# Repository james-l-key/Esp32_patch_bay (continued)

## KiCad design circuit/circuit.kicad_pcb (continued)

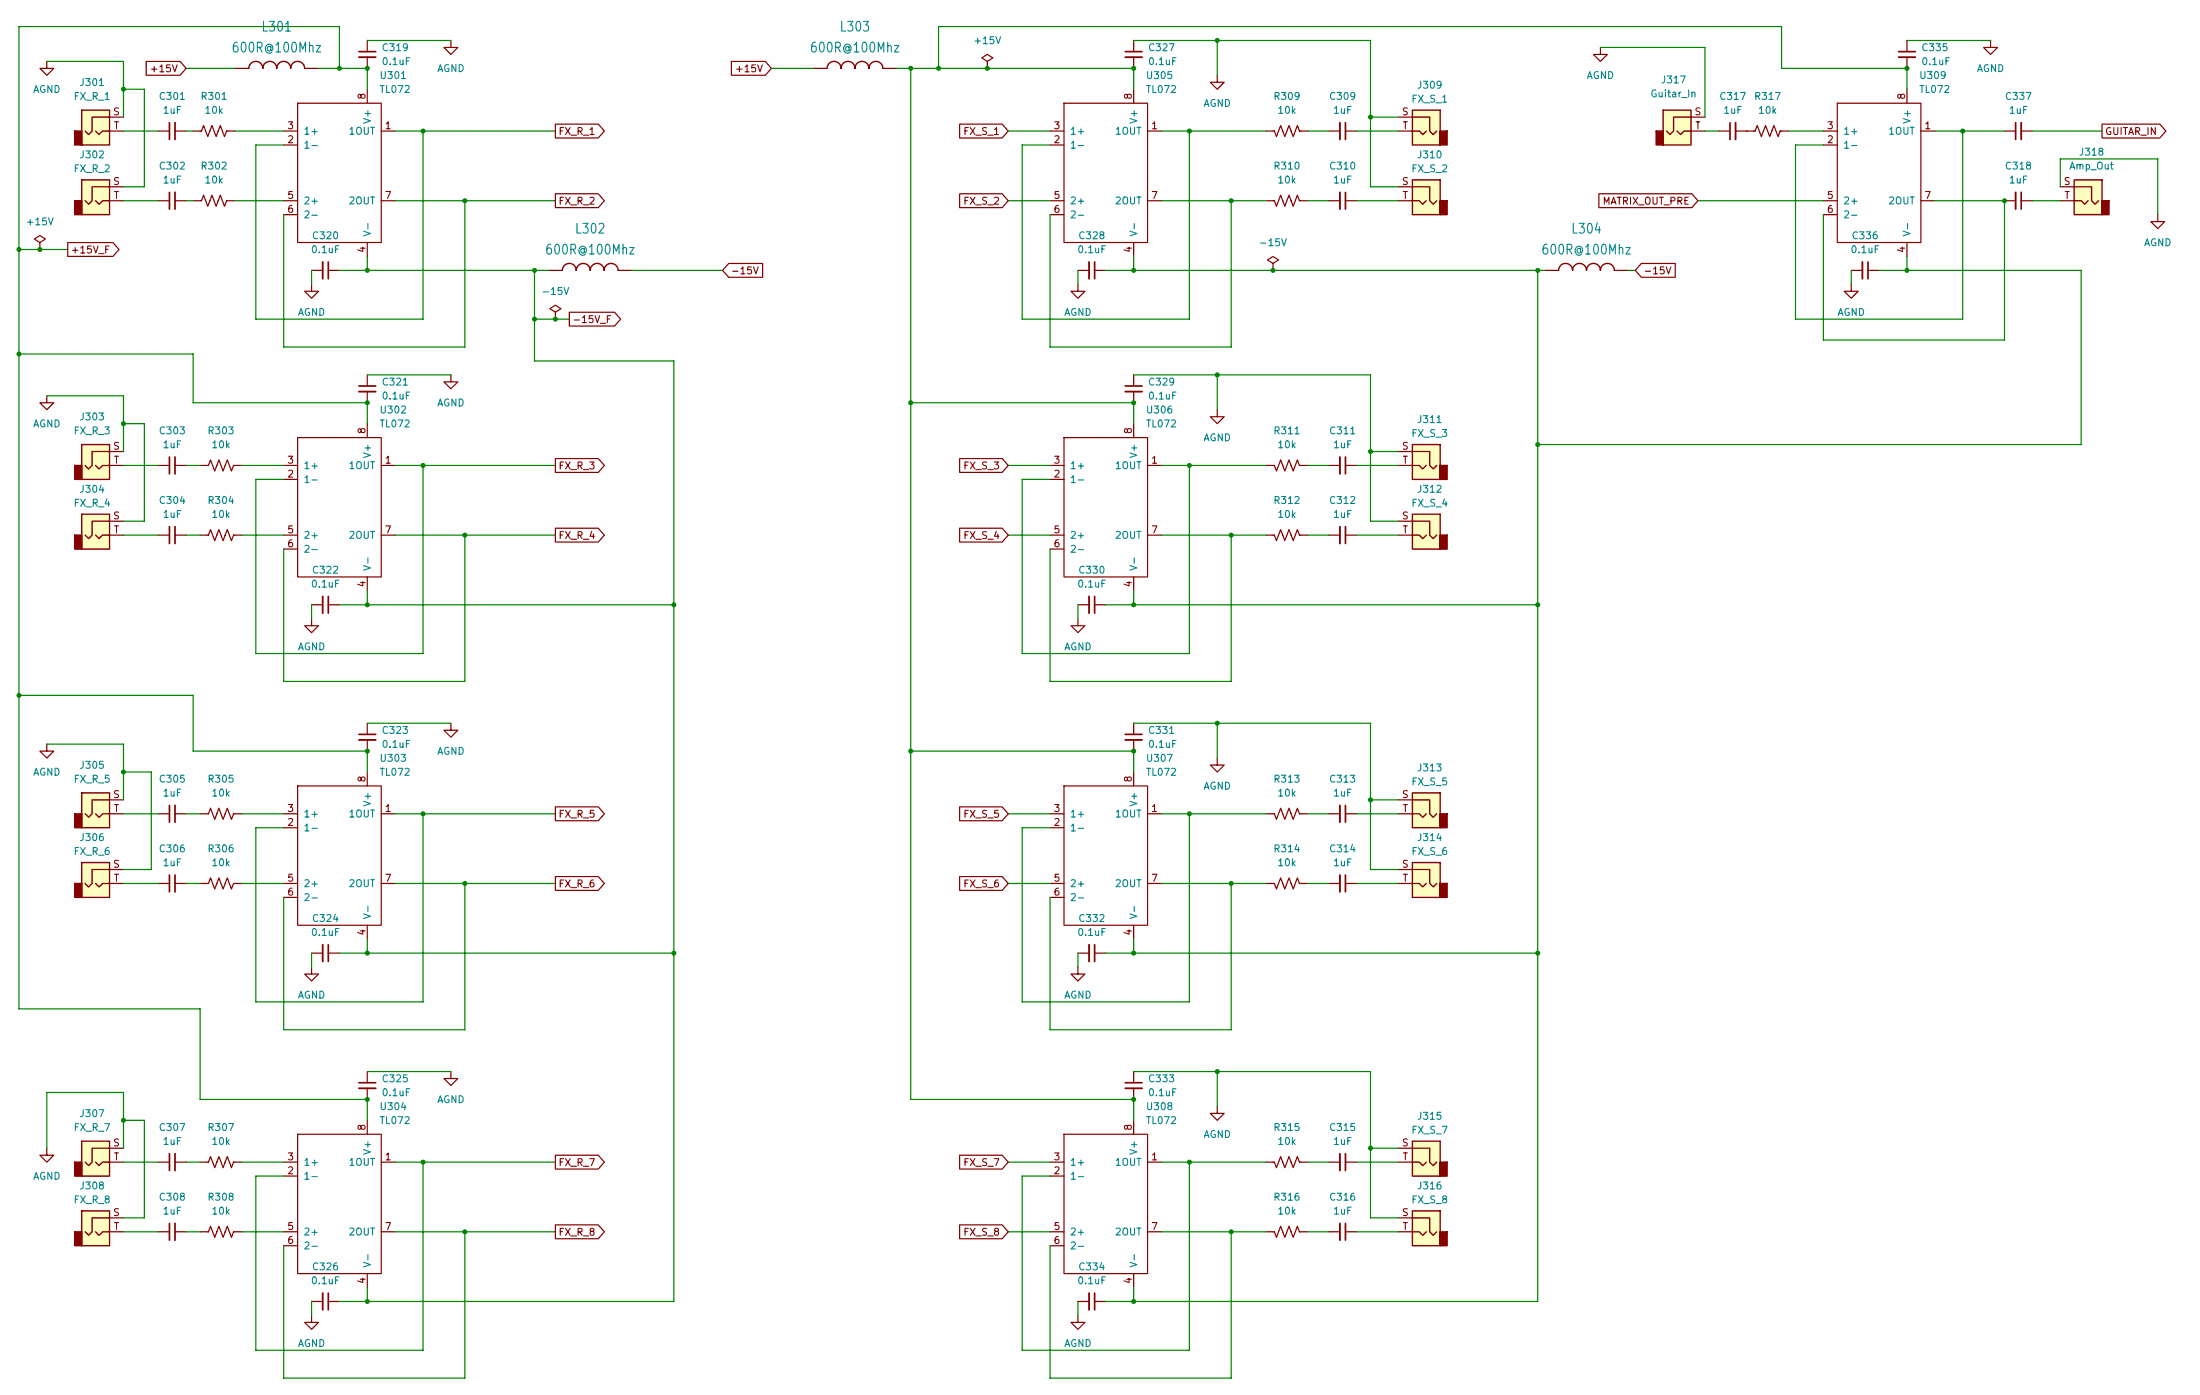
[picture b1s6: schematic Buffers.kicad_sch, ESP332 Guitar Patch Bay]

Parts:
C301, C302, C303, C304, C305, C306, C307, C308, C309, C310, C311, C312, C313, C314, C315, C316, C317, C318, C337: 1uF; C_Disc_D5.0mm_W2.5mm_P2.50mm
C319, C320, C321, C322, C323, C324, C325, C326, C327, C328, C329, C330, C331, C332, C333, C334, C335, C336: 0.1uF; C_Disc_D5.0mm_W2.5mm_P2.50mm
J301: FX_R_1; Jack
J302: FX_R_2; Jack
J303: FX_R_3; Jack
J304: FX_R_4; Jack
J305: FX_R_5; Jack
J306: FX_R_6; Jack
J307: FX_R_7; Jack
J308: FX_R_8; Jack
J309: FX_S_1; Jack
J310: FX_S_2; Jack
J311: FX_S_3; Jack
J312: FX_S_4; Jack
J313: FX_S_5; Jack
J314: FX_S_6; Jack
J315: FX_S_7; Jack
J316: FX_S_8; Jack
J317: Guitar_In; Jack
J318: Amp_Out; Jack
L301, L302, L303, L304: 600R@100Mhz; WE-UKW_74275010
R301, R302, R303, R304, R305, R306, R307, R308, R309, R310, R311, R312, R313, R314, R315, R316, R317: 10k; R_Axial_DIN0207_L6.3mm_D2.5mm_P7.62mm_Horizontal
U301, U302, U303, U304, U305, U306, U307, U308, U309: TL072; DIP-8_W7.62mm

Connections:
+15V: L301.2, L303.1; also elsewhere on the board
+15V_F: C319.2, C321.2, C323.2, C325.2, L301.1, U301.8 (V+), U302.8 (V+), U303.8 (V+), U304.8 (V+); also elsewhere on the board
-15V: L302.1, L304.2; also elsewhere on the board
-15V_F: C320.1, C322.1, C324.1, C326.1, L302.2, U301.4 (V-), U302.4 (V-), U303.4 (V-), U304.4 (V-); also elsewhere on the board
AGND: C319.1, C320.2, C321.1, C322.2, C323.1, C324.2, C325.1, C326.2, C327.1, C328.2, C329.1, C330.2, C331.1, C332.2, C333.1, C334.2, C335.1, C336.2, J301.S, J302.S, J303.S, J304.S, J305.S, J306.S, J307.S, J308.S, J309.S, J310.S, J311.S, J312.S, J313.S, J314.S, J315.S, J316.S, J317.S, J318.S; also elsewhere on the board
FX_R_1: U301.1 (1OUT), U301.2 (1-); also elsewhere on the board
FX_R_2: U301.6 (2-), U301.7 (2OUT); also elsewhere on the board
FX_R_3: U302.1 (1OUT), U302.2 (1-); also elsewhere on the board
FX_R_4: U302.6 (2-), U302.7 (2OUT); also elsewhere on the board
FX_R_5: U303.1 (1OUT), U303.2 (1-); also elsewhere on the board
FX_R_6: U303.6 (2-), U303.7 (2OUT); also elsewhere on the board
FX_R_7: U304.1 (1OUT), U304.2 (1-); also elsewhere on the board
FX_R_8: U304.6 (2-), U304.7 (2OUT); also elsewhere on the board
FX_S_1: U305.3 (1+); also elsewhere on the board
FX_S_2: U305.5 (2+); also elsewhere on the board
FX_S_3: U306.3 (1+); also elsewhere on the board
FX_S_4: U306.5 (2+); also elsewhere on the board
FX_S_5: U307.3 (1+); also elsewhere on the board
FX_S_6: U307.5 (2+); also elsewhere on the board
FX_S_7: U308.3 (1+); also elsewhere on the board
FX_S_8: U308.5 (2+); also elsewhere on the board
GUITAR_IN: C337.2; also elsewhere on the board
MATRIX_OUT_PRE: U309.5 (2+); also elsewhere on the board
unnamed: C301.1, J301.T
unnamed: C301.2, R301.2
unnamed: C302.1, J302.T
unnamed: C302.2, R302.2
unnamed: C303.1, J303.T
unnamed: C303.2, R303.2
unnamed: C304.1, J304.T
unnamed: C304.2, R304.2
unnamed: C305.1, J305.T
unnamed: C305.2, R305.2
unnamed: C306.1, J306.T
unnamed: C306.2, R306.2
unnamed: C307.1, J307.T
unnamed: C307.2, R307.2
unnamed: C308.1, J308.T
unnamed: C308.2, R308.2
unnamed: C309.1, J309.T
unnamed: C309.2, R309.2
unnamed: C310.1, J310.T
unnamed: C310.2, R310.2
unnamed: C311.1, J311.T
unnamed: C311.2, R311.2
unnamed: C312.1, J312.T
unnamed: C312.2, R312.2
unnamed: C313.1, J313.T
unnamed: C313.2, R313.2
unnamed: C314.1, J314.T
unnamed: C314.2, R314.2
unnamed: C315.1, J315.T
unnamed: C315.2, R315.2
unnamed: C316.1, J316.T
unnamed: C316.2, R316.2
unnamed: C317.1, J317.T
unnamed: C317.2, R317.2
unnamed: C318.1, J318.T
unnamed: R301.1, U301.3 (1+)
unnamed: R302.1, U301.5 (2+)
unnamed: R303.1, U302.3 (1+)
unnamed: R304.1, U302.5 (2+)
unnamed: R305.1, U303.3 (1+)
unnamed: R306.1, U303.5 (2+)
unnamed: R307.1, U304.3 (1+)
unnamed: R308.1, U304.5 (2+)
unnamed: R309.1, U305.1 (1OUT), U305.2 (1-)
unnamed: R310.1, U305.6 (2-), U305.7 (2OUT)
unnamed: C327.2, C329.2, C331.2, C333.2, C335.2, L303.2, U305.8 (V+), U306.8 (V+), U307.8 (V+), U308.8 (V+), U309.8 (V+)
unnamed: C328.1, C330.1, C332.1, C334.1, C336.1, L304.1, U305.4 (V-), U306.4 (V-), U307.4 (V-), U308.4 (V-), U309.4 (V-)
unnamed: R311.1, U306.1 (1OUT), U306.2 (1-)
unnamed: R312.1, U306.6 (2-), U306.7 (2OUT)
unnamed: R313.1, U307.1 (1OUT), U307.2 (1-)
unnamed: R314.1, U307.6 (2-), U307.7 (2OUT)
unnamed: R315.1, U308.1 (1OUT), U308.2 (1-)
unnamed: R316.1, U308.6 (2-), U308.7 (2OUT)
unnamed: R317.1, U309.3 (1+)
unnamed: C337.1, U309.1 (1OUT), U309.2 (1-)
unnamed: C318.2, U309.6 (2-), U309.7 (2OUT)

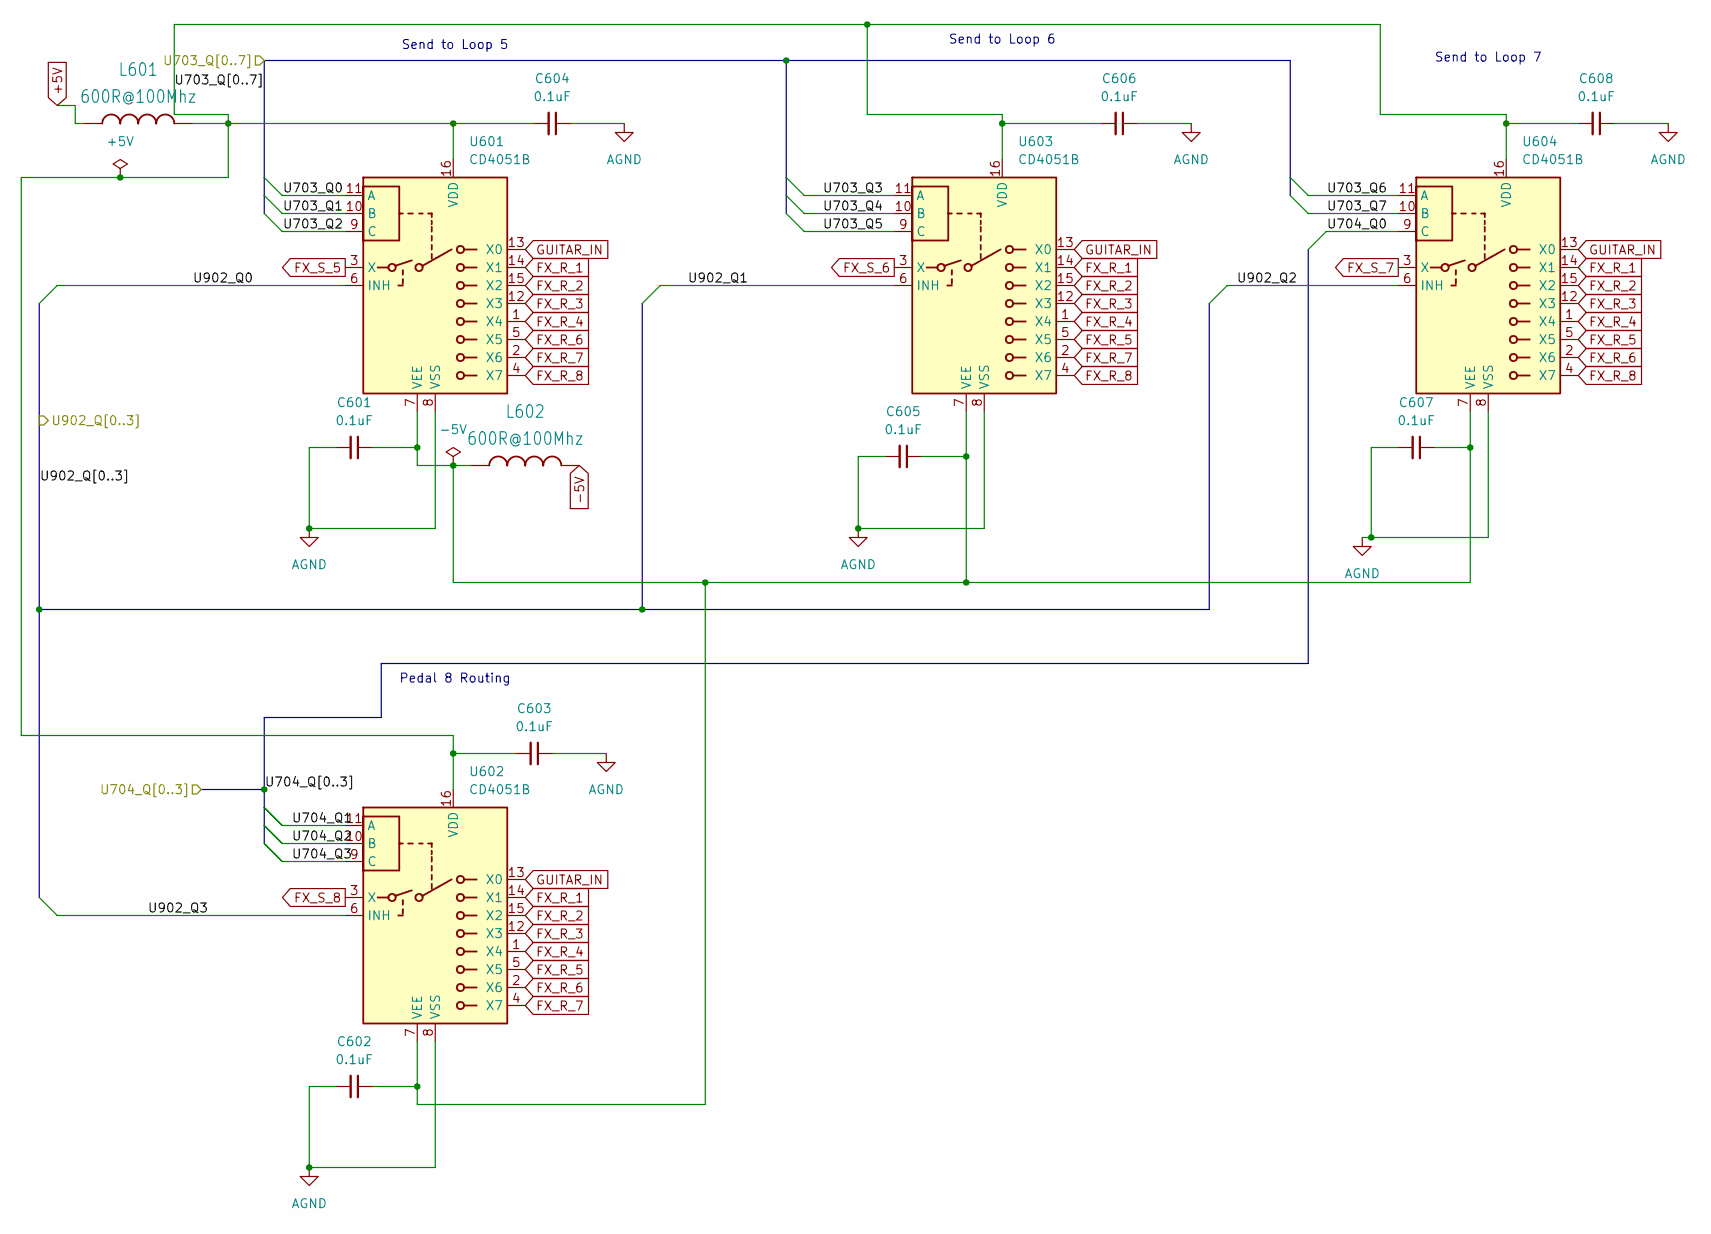
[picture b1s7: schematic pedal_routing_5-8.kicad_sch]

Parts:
C601, C602, C603, C604, C605, C606, C607, C608: 0.1uF; C_Disc_D5.0mm_W2.5mm_P2.50mm
L601, L602: 600R@100Mhz; WE-UKW_74275010
U601, U602, U603, U604: CD4051B; DIP-16_W7.62mm

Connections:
+5V: L601.1; also elsewhere on the board
-5V: L602.2; also elsewhere on the board
/Inhibit Registers/U902_Q0: U601.6 (INH); also elsewhere on the board
/Inhibit Registers/U902_Q1: U603.6 (INH); also elsewhere on the board
/Inhibit Registers/U902_Q2: U604.6 (INH); also elsewhere on the board
/Inhibit Registers/U902_Q3: U602.6 (INH); also elsewhere on the board
/Matrix Shift Registers/U703_Q0: U601.11 (A); also elsewhere on the board
/Matrix Shift Registers/U703_Q1: U601.10 (B); also elsewhere on the board
/Matrix Shift Registers/U703_Q2: U601.9 (C); also elsewhere on the board
/Matrix Shift Registers/U703_Q3: U603.11 (A); also elsewhere on the board
/Matrix Shift Registers/U703_Q4: U603.10 (B); also elsewhere on the board
/Matrix Shift Registers/U703_Q5: U603.9 (C); also elsewhere on the board
/Matrix Shift Registers/U703_Q6: U604.11 (A); also elsewhere on the board
/Matrix Shift Registers/U703_Q7: U604.10 (B); also elsewhere on the board
/Matrix Shift Registers/U704_Q0: U604.9 (C); also elsewhere on the board
/Matrix Shift Registers/U704_Q1: U602.11 (A); also elsewhere on the board
/Matrix Shift Registers/U704_Q2: U602.10 (B); also elsewhere on the board
/Matrix Shift Registers/U704_Q3: U602.9 (C); also elsewhere on the board
AGND: C601.2, C602.2, C603.1, C604.1, C605.2, C606.1, C607.2, C608.1, U601.8 (VSS), U602.8 (VSS), U603.8 (VSS), U604.8 (VSS); also elsewhere on the board
FX_R_1: U601.14 (X1), U602.14 (X1), U603.14 (X1), U604.14 (X1); also elsewhere on the board
FX_R_2: U601.15 (X2), U602.15 (X2), U603.15 (X2), U604.15 (X2); also elsewhere on the board
FX_R_3: U601.12 (X3), U602.12 (X3), U603.12 (X3), U604.12 (X3); also elsewhere on the board
FX_R_4: U601.1 (X4), U602.1 (X4), U603.1 (X4), U604.1 (X4); also elsewhere on the board
FX_R_5: U602.5 (X5), U603.5 (X5), U604.5 (X5); also elsewhere on the board
FX_R_6: U601.5 (X5), U602.2 (X6), U604.2 (X6); also elsewhere on the board
FX_R_7: U601.2 (X6), U602.4 (X7), U603.2 (X6); also elsewhere on the board
FX_R_8: U601.4 (X7), U603.4 (X7), U604.4 (X7); also elsewhere on the board
FX_S_5: U601.3 (X); also elsewhere on the board
FX_S_6: U603.3 (X); also elsewhere on the board
FX_S_7: U604.3 (X); also elsewhere on the board
FX_S_8: U602.3 (X); also elsewhere on the board
GUITAR_IN: U601.13 (X0), U602.13 (X0), U603.13 (X0), U604.13 (X0); also elsewhere on the board
unnamed: C603.2, C604.2, C606.2, C608.2, L601.2, U601.16 (VDD), U602.16 (VDD), U603.16 (VDD), U604.16 (VDD)
unnamed: C601.1, C602.1, C605.1, C607.1, L602.1, U601.7 (VEE), U602.7 (VEE), U603.7 (VEE), U604.7 (VEE)

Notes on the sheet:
Pedal 8 Routing
Send to Loop 5
Send to Loop 6
Send to Loop 7

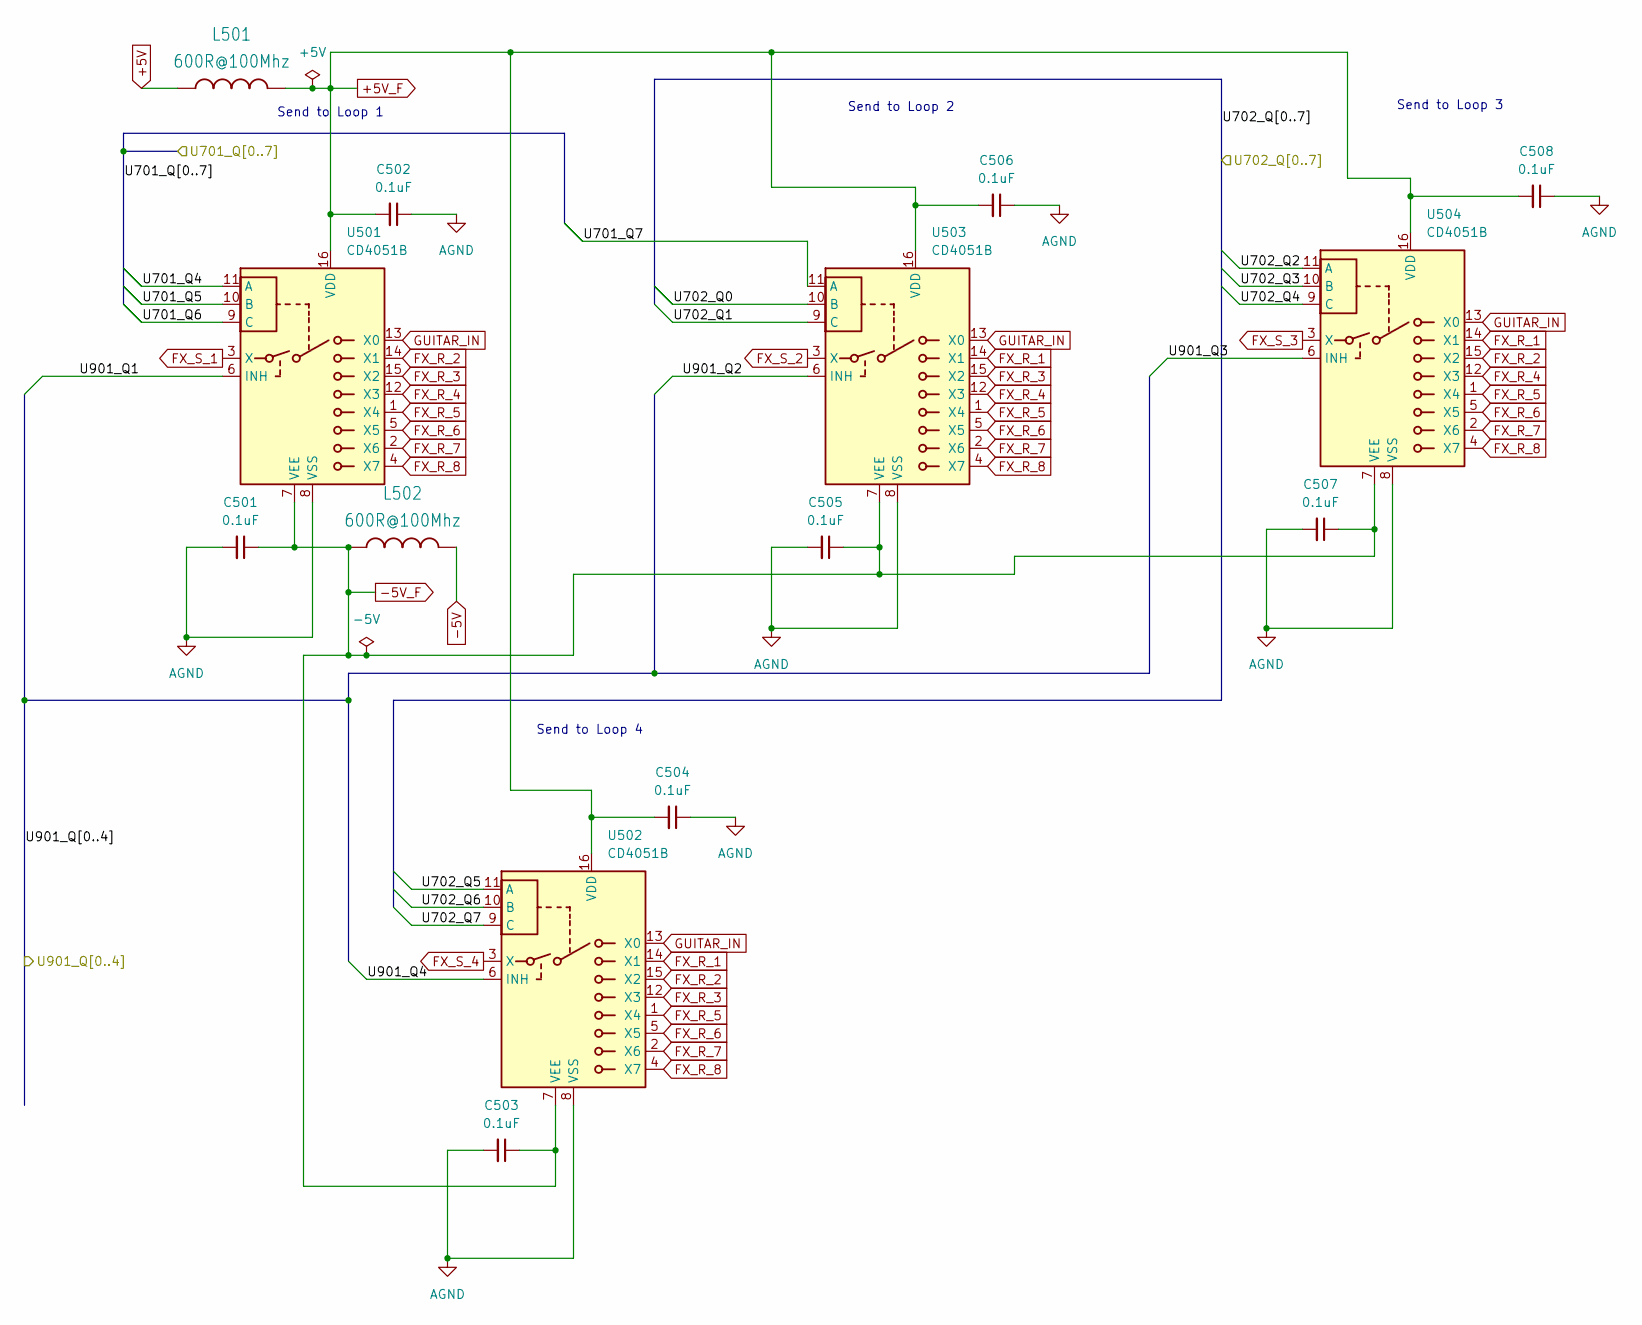
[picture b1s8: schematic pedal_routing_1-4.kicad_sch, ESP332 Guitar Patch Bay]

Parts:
C501, C502, C503, C504, C505, C506, C507, C508: 0.1uF; C_Disc_D5.0mm_W2.5mm_P2.50mm
L501, L502: 600R@100Mhz; WE-UKW_74275010
U501, U502, U503, U504: CD4051B; DIP-16_W7.62mm

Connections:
+5V: L501.1; also elsewhere on the board
+5V_F: C502.2, C504.2, C506.2, C508.2, L501.2, U501.16 (VDD), U502.16 (VDD), U503.16 (VDD), U504.16 (VDD); also elsewhere on the board
-5V: L502.2; also elsewhere on the board
-5V_F: C501.1, C503.1, C505.1, C507.1, L502.1, U501.7 (VEE), U502.7 (VEE), U503.7 (VEE), U504.7 (VEE); also elsewhere on the board
/IO Routing/U701_Q4: U501.11 (A); also elsewhere on the board
/IO Routing/U701_Q5: U501.10 (B); also elsewhere on the board
/IO Routing/U701_Q6: U501.9 (C); also elsewhere on the board
/IO Routing/U701_Q7: U503.11 (A); also elsewhere on the board
/IO Routing/U901_Q1: U501.6 (INH); also elsewhere on the board
/IO Routing/U901_Q2: U503.6 (INH); also elsewhere on the board
/IO Routing/U901_Q3: U504.6 (INH); also elsewhere on the board
/IO Routing/U901_Q4: U502.6 (INH); also elsewhere on the board
/Matrix Shift Registers/U702_Q0: U503.10 (B); also elsewhere on the board
/Matrix Shift Registers/U702_Q1: U503.9 (C); also elsewhere on the board
/Matrix Shift Registers/U702_Q2: U504.11 (A); also elsewhere on the board
/Matrix Shift Registers/U702_Q3: U504.10 (B); also elsewhere on the board
/Matrix Shift Registers/U702_Q4: U504.9 (C); also elsewhere on the board
/Matrix Shift Registers/U702_Q5: U502.11 (A); also elsewhere on the board
/Matrix Shift Registers/U702_Q6: U502.10 (B); also elsewhere on the board
/Matrix Shift Registers/U702_Q7: U502.9 (C); also elsewhere on the board
AGND: C501.2, C502.1, C503.2, C504.1, C505.2, C506.1, C507.2, C508.1, U501.8 (VSS), U502.8 (VSS), U503.8 (VSS), U504.8 (VSS); also elsewhere on the board
FX_R_1: U502.14 (X1), U503.14 (X1), U504.14 (X1); also elsewhere on the board
FX_R_2: U501.14 (X1), U502.15 (X2), U504.15 (X2); also elsewhere on the board
FX_R_3: U501.15 (X2), U502.12 (X3), U503.15 (X2); also elsewhere on the board
FX_R_4: U501.12 (X3), U503.12 (X3), U504.12 (X3); also elsewhere on the board
FX_R_5: U501.1 (X4), U502.1 (X4), U503.1 (X4), U504.1 (X4); also elsewhere on the board
FX_R_6: U501.5 (X5), U502.5 (X5), U503.5 (X5), U504.5 (X5); also elsewhere on the board
FX_R_7: U501.2 (X6), U502.2 (X6), U503.2 (X6), U504.2 (X6); also elsewhere on the board
FX_R_8: U501.4 (X7), U502.4 (X7), U503.4 (X7), U504.4 (X7); also elsewhere on the board
FX_S_1: U501.3 (X); also elsewhere on the board
FX_S_2: U503.3 (X); also elsewhere on the board
FX_S_3: U504.3 (X); also elsewhere on the board
FX_S_4: U502.3 (X); also elsewhere on the board
GUITAR_IN: U501.13 (X0), U502.13 (X0), U503.13 (X0), U504.13 (X0); also elsewhere on the board

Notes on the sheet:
Send to Loop 2
Send to Loop 3
Send to Loop 4
Send to Loop 1

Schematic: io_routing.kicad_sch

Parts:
C401, C402, C403, C404, C405: 0.1uF; C_Disc_D5.0mm_W2.5mm_P2.50mm
U401: ADG419BN; DIP-8_W7.62mm
U402: CD4051B; DIP-16_W7.62mm

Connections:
+5V_F: C403.1, C405.2, U401.5 (VL), U402.16 (VDD); also elsewhere on the board
+15V_F: C401.1, U401.4 (V+); also elsewhere on the board
-5V_F: C404.1, U402.7 (VEE); also elsewhere on the board
-15V_F: C402.1, U401.7 (V-); also elsewhere on the board
/IO Routing/U701_Q0: U401.6; also elsewhere on the board
/IO Routing/U701_Q1: U402.11 (A); also elsewhere on the board
/IO Routing/U701_Q2: U402.10 (B); also elsewhere on the board
/IO Routing/U701_Q3: U402.9 (C); also elsewhere on the board
/IO Routing/U901_Q0: U402.6 (INH); also elsewhere on the board
AGND: C401.2, C402.2, C403.2, C404.2, C405.1, U401.3 (GND), U402.8 (VSS); also elsewhere on the board
FX_R_1: U402.13 (X0); also elsewhere on the board
FX_R_2: U402.14 (X1); also elsewhere on the board
FX_R_3: U402.15 (X2); also elsewhere on the board
FX_R_4: U402.12 (X3); also elsewhere on the board
FX_R_5: U402.1 (X4); also elsewhere on the board
FX_R_6: U402.5 (X5); also elsewhere on the board
FX_R_7: U402.2 (X6); also elsewhere on the board
FX_R_8: U402.4 (X7); also elsewhere on the board
GUITAR_IN: U401.8; also elsewhere on the board
MATRIX_OUT_PRE: U401.1; also elsewhere on the board
unnamed: U401.2, U402.3 (X)

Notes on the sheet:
Output Mux 1

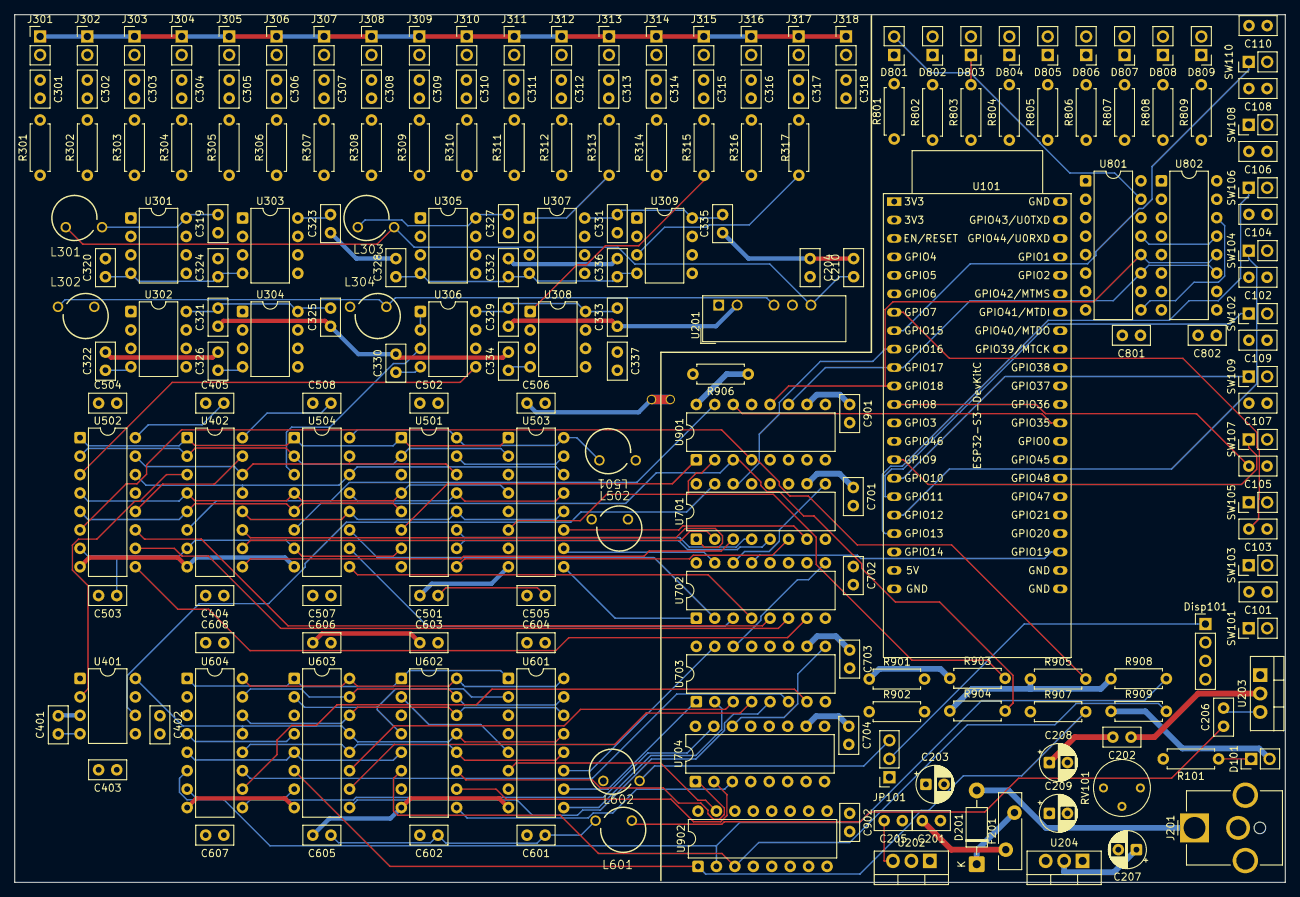
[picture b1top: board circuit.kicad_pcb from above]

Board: 4 copper layers, 175.0 x 119.5 mm, 207 parts (0 on the bottom side), 178 nets.

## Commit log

2025-05-17 Initial Documentation
2025-05-19 Moved circuit.kikad_sch and made changes to matrix routhing. WIP
2025-05-19 addendum
2025-05-21 Update circuit.kicad_sch
    Swapped DG408 for CD4051B
2025-05-22 Update circuit.kicad_sch
    Added Power supplies and Nets.
2025-05-23 Circuit nearly complete. Need more decoupling Caps.
2025-05-24 Continued prgress on circuit. Split digital and analog gnd.
2025-05-25 Editing Circuit for readability.
2025-05-25 Rebuilt bus and matrix.
2025-05-26 Hopefully close to finished
2025-05-27 Create LICENSE
2025-05-28 Created pdf and made minor readabilty changes.
2025-05-30 Changed default pin assignments and setp sdkconfig.defaults
2025-05-31 Added LEDs and shift registers
2025-06-01 Very tentative PCB layout, Code compiles but needs major functionality testing.
2025-06-04 Rebuilt Matrix and added inhibit function.
    Matrix was flawed, It now supports 8 FX loops (pedals) in any order. Or optionally none at all with a buffered bypass, or anywhere in between. The inhibit function will allow the option to press any 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
2025-06-05 Re-annotation of circuit, new PCB routing, updated PDF
2025-06-07 Fine tuning of circuit
    Added jumper to select voltage of display, changed 3.3V regulator from SMD to TO-220 to simplify DIY builds.
2025-06-10 Added ferrite beads and tweaked PCB
2025-06-15 Circuit tweaks and PCB
2025-06-15 Update circuit.pdf
    Update before clean up.
2025-06-15 Labels for headers on PCB
2025-06-16 removal of Circuit to create submodule
2025-06-16 Added circuit as submodule
2025-06-16 Added led controls
2025-06-16 Update CMakeLists.txt
    Removed erroneous file reterences
